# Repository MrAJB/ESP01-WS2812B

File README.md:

## Introduction
This repo documents the development of a small ESP-01 breakout board to support controlling two WS2812B LED strips and a Dallas DS18B20 temperature sensor. This allows for easy integration with HomeAssistant through ESPHome. 

Note that I'm just developing this stuff in my spare time and I'm far from an expert. Development may be slow and I cannot make any promises on the quality of this board. However, feel free to look around, maybe there's something useful for you in there!

## Hardware Overview
A schematic overview of the breakout board can be found [here](Hardware/esp01-ws2812b-breakout.pdf). As an be seen, this simple board allows to fit an ESP-01. Furthermore, it contains two level-shifters to control 5V data lines. The board is prepared to mount a DS18B20 temperature sensor, if desired. Lastly, a header to interface with the GPIO0 pin can be added, to further expand this board.

The layout and routing of V1 are finished:

(Note: the cutout in the lower left section aims to provide clearance for the WiFi antenna to improve the ESP's WiFi range.)

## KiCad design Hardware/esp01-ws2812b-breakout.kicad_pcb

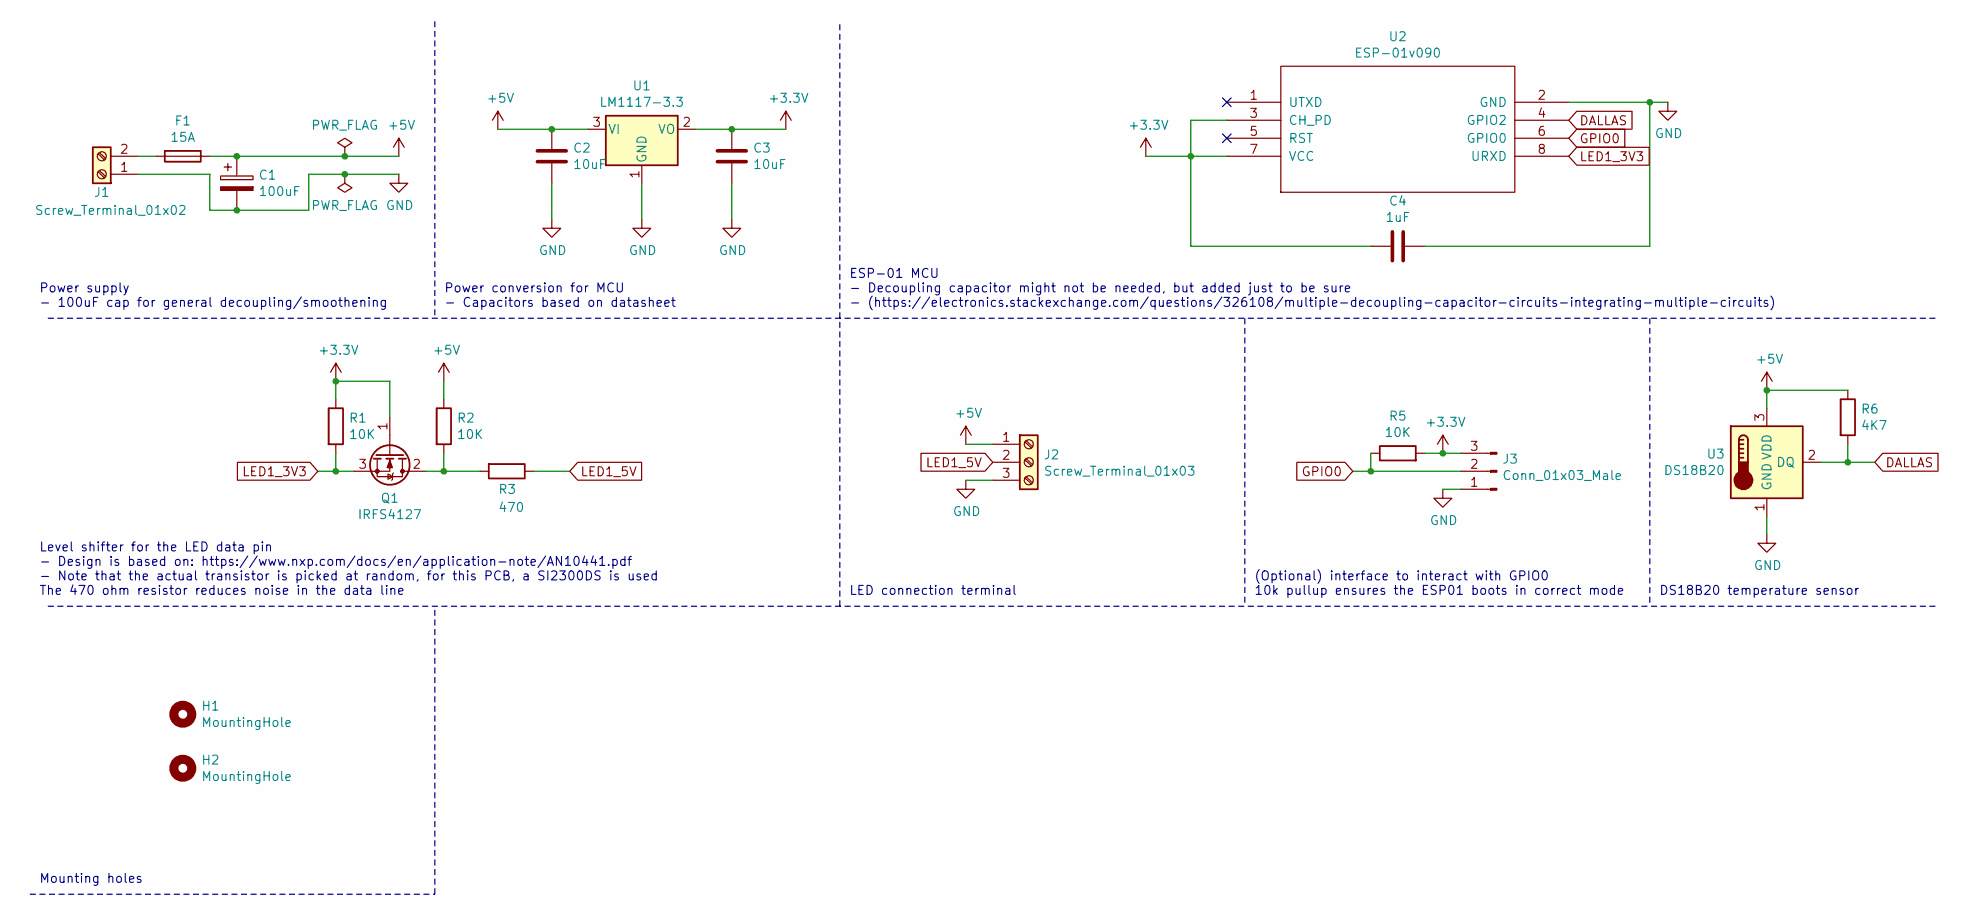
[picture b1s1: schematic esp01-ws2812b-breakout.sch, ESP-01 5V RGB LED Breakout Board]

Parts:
C1: 100uF; CP_Radial_D5.0mm_P2.00mm
C2, C3: 10uF; C_0805_2012Metric_Pad1.18x1.45mm_HandSolder
C4: 1uF; C_0805_2012Metric_Pad1.18x1.45mm_HandSolder
F1: 15A; 1808_SMD_Fuse_Holder
H1, H2: MountingHole; MountingHole_2.2mm_M2
J1: Screw_Terminal_01x02; 0102-blue-terminal
J2: Screw_Terminal_01x03; 0103-blue-terminal
J3: Conn_01x03_Male; PinHeader_1x03_P2.54mm_Vertical
Q1: IRFS4127; SOT-23_DS-REVERSED
R1, R2, R5: 10K; R_0805_2012Metric_Pad1.20x1.40mm_HandSolder
R3: 470; R_0805_2012Metric_Pad1.20x1.40mm_HandSolder
R6: 4K7; R_0805_2012Metric_Pad1.20x1.40mm_HandSolder
U1: LM1117-3.3; SOT-223
U2: ESP-01v090; ESP-01
U3: DS18B20; TO-92_Inline

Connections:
+3V3: C3.1, C4.2, J3.3, Q1.1 (G), R1.1, R5.2, U1.2 (VO), U2.3 (CH_PD), U2.7 (VCC)
+5V: C1.1, C2.1, F1.1, J2.1, R2.1, R6.1, U1.3 (VI), U3.3 (VDD)
DALLAS: R6.2, U2.4 (GPIO2), U3.2 (DQ)
GND: C1.2, C2.2, C3.2, C4.1, J1.1, J2.3, J3.1, U1.1 (GND), U2.2 (GND), U3.1 (GND)
GPIO0: J3.2, R5.1, U2.6 (GPIO0)
LED1_3V3: Q1.3 (S), R1.2, U2.8 (URXD)
LED1_5V: J2.2, R3.1
unnamed: F1.2, J1.2
unnamed: Q1.2 (D), R2.2, R3.2

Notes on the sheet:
ESP-01 MCU - Decoupling capacitor might not be needed, but added just to be sure - (https://electronics.stackexchange.com/questions/326108/multiple-decoupling-capacitor-circuits-integrating-multiple-circuits)
Level shifter for the LED data pin - Design is based on: https://www.nxp.com/docs/en/application-note/AN10441.pdf - Note that the actual transistor is picked at random, for this PCB, a SI2300DS is used The 470 ohm resistor reduces noise in the data line
LED connection terminal
DS18B20 temperature sensor
Mounting holes
(Optional) interface to interact with GPIO0 10k pullup ensures the ESP01 boots in correct mode
Power conversion for MCU - Capacitors based on datasheet
Power supply - 100uF cap for general decoupling/smoothening

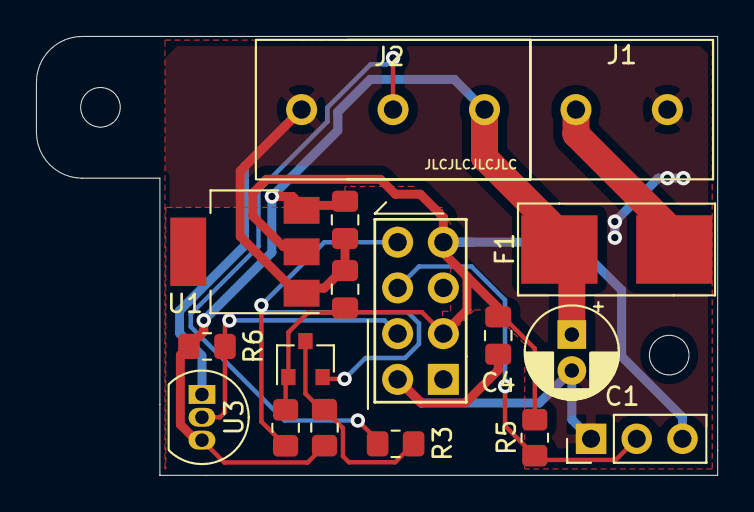
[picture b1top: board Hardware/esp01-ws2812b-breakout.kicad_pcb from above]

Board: 2 copper layers, 37.8 x 24.4 mm, 19 parts (0 on the bottom side), 9 nets.

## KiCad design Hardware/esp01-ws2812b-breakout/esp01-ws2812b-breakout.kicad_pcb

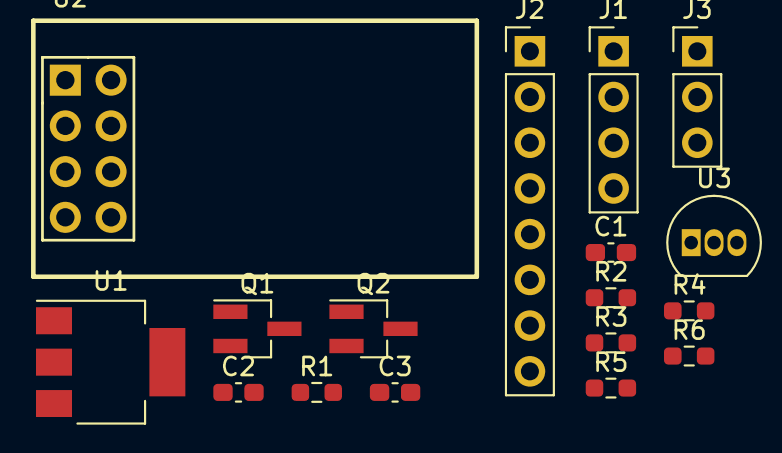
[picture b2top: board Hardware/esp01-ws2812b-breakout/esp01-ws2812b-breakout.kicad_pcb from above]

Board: 2 copper layers, 17 parts (0 on the bottom side), 9 nets, no tracks yet.

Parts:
C1, C2: 10uF; C_0603_1608Metric_Pad1.08x0.95mm_HandSolder
C3: 100uF; C_0603_1608Metric_Pad1.08x0.95mm_HandSolder
J1: Screw_Terminal_01x02; PinHeader_1x04_P2.54mm_Vertical
J2: Screw_Terminal_01x04; PinHeader_1x08_P2.54mm_Vertical
J3: Conn_01x03_Male; PinHeader_1x03_P2.54mm_Vertical
Q1, Q2: IRFS4127; SOT-23_Handsoldering_DS-REVERSED
R1, R2, R3, R4, R5: 10K; R_0603_1608Metric_Pad0.98x0.95mm_HandSolder
R6: 4K7; R_0603_1608Metric_Pad0.98x0.95mm_HandSolder
U1: LM1117-3.3; SOT-223
U2: ESP-01v090; ESP-01
U3: DS18B20; TO-92_Inline

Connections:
+3V3: C2.1, J3.2, J3.3, Q1.1, Q2.1, R1.1, R3.1, R5.2, U1.2, U2.3, U2.7
+5V: C1.1, C3.1, J1.2, J2.1, R2.1, R4.1, R6.1, U1.3, U3.3
DALLAS: R6.2, U2.4, U3.2
GND: C1.2, C2.2, C3.2, J1.1, J2.4, J3.1, U1.1, U2.2, U3.1
GPIO0: R5.1, U2.6
LED1_3V3: Q1.3, R1.2, U2.1
LED1_5V: J2.2, Q1.2, R2.2
LED2_3V3: Q2.3, R3.2, U2.8
LED2_5V: J2.3, Q2.2, R4.2

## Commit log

2020-12-20 PCB schematic created
2020-12-21 Included level shifters for LED data pins
2020-12-21 Schematics completed, PCB design started
2020-12-21 Deleted redundant README files
2020-12-21 Moved KiCad files to root hardware folder
2020-12-21 Added most used datasheets
2020-12-21 Updated capacitor footprint and NETlist
2020-12-21 Updated custom footprint libraries
2020-12-21 Finished PCB layout
2020-12-23 Changed decoupling capacitors layout
2020-12-23 Defined footprints and added SMD fuse print
2020-12-23 Finished schematics and footprint revisions
2020-12-23 Resistor footprints were still 0603, fixed now.
2020-12-23 Antenna clearance, redid layout
    Some sources comment that the ESP8266's WiFi range can be extended dramatically by having the antenna 'sticking' out from the PCB. So I decided to inplement that. Additionally, the new footprints req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
2020-12-23 Updated PDF schematic
2020-12-23 Layout updates
2020-12-23 Fixed schematic of pull-up resistor
2020-12-23 Started routing
2020-12-23 Continued routing
2020-12-29 Finished PCB routing
2020-12-29 Finalized PCB layout, added PDF+PNG
2021-10-08 Checked an finalized designs for production
2021-10-08 Generated production files
2021-10-08 No real changes, just save the files
2021-11-25 Removed second LED channel
2021-12-02 Updated to correct LED pin
2021-12-02 Started re-doing the PCB layout
2021-12-03 Updated PCB layout, removed obsolete traces
2021-12-10 Updated schematic export, finished PCB design
2021-12-10 Cosmetic tweaks
2021-12-10 Generated STEP export of PCB
